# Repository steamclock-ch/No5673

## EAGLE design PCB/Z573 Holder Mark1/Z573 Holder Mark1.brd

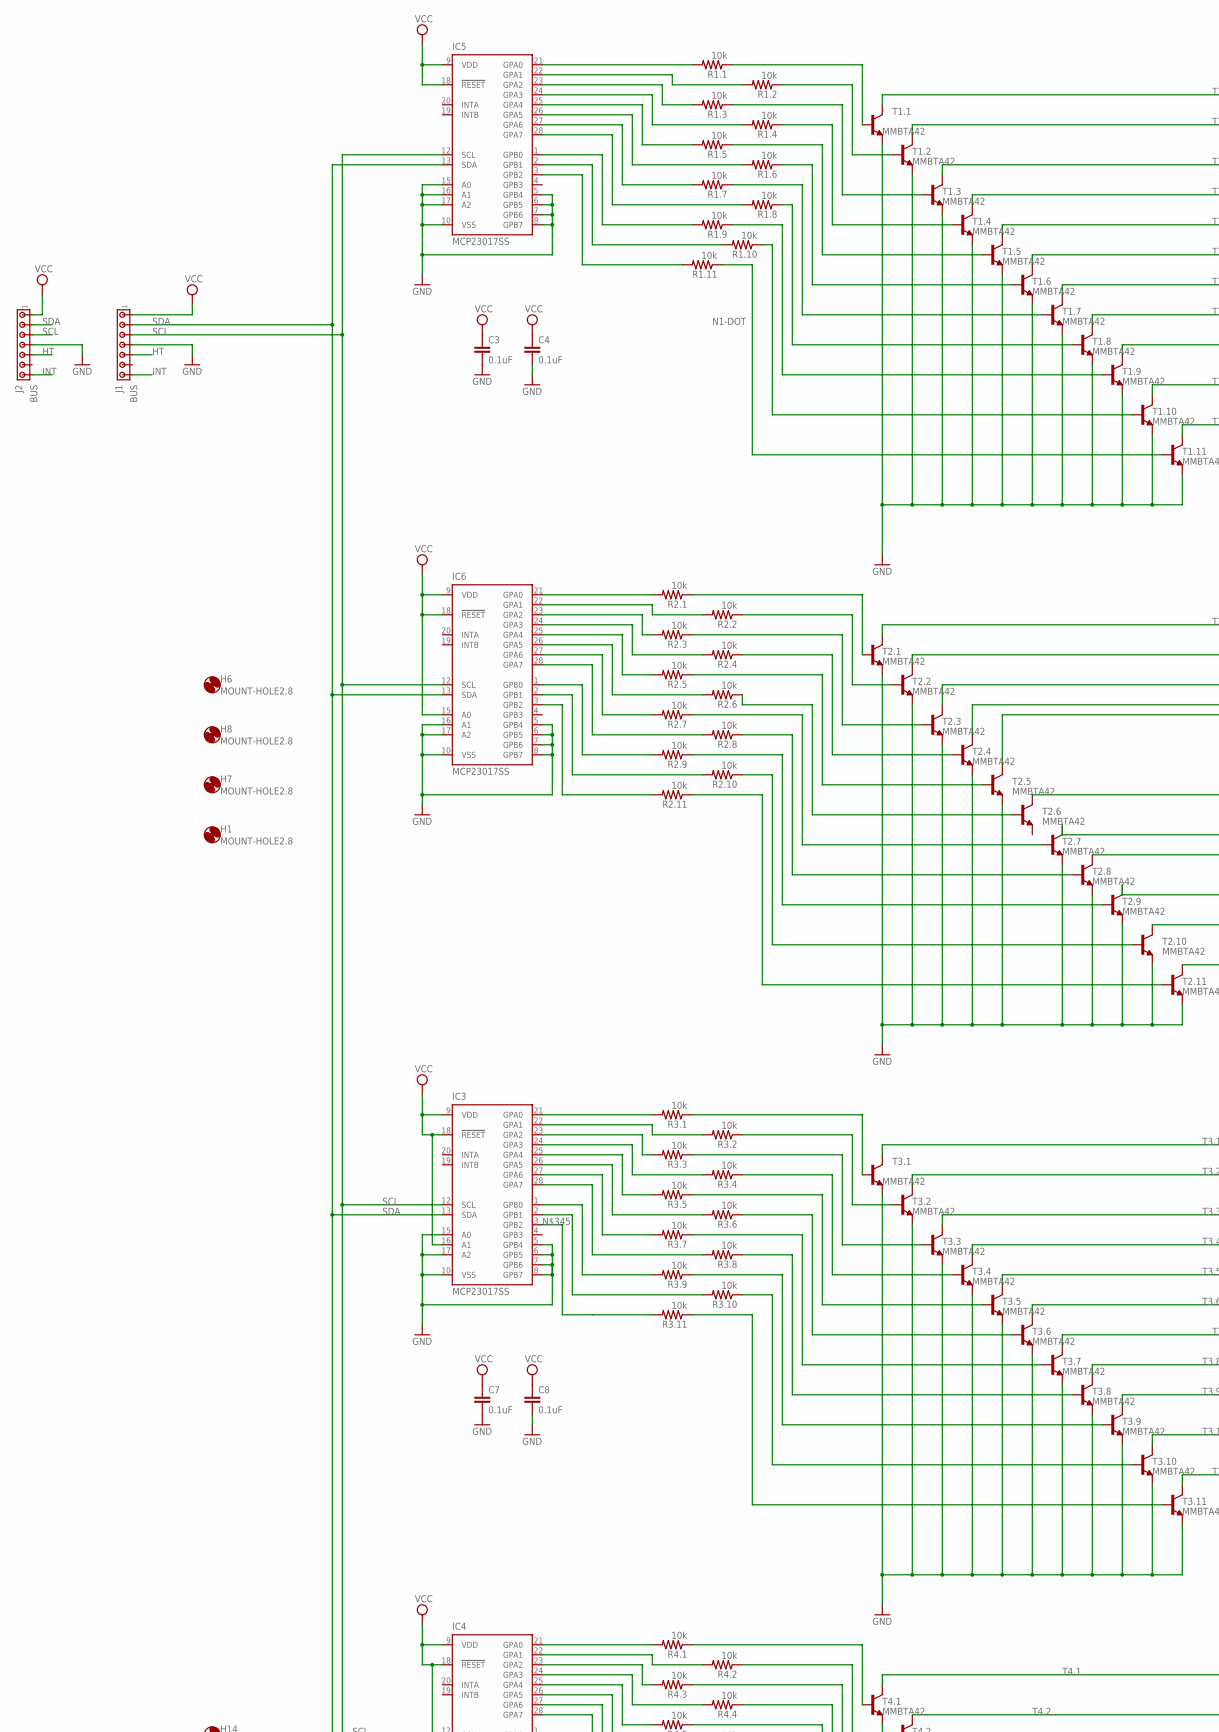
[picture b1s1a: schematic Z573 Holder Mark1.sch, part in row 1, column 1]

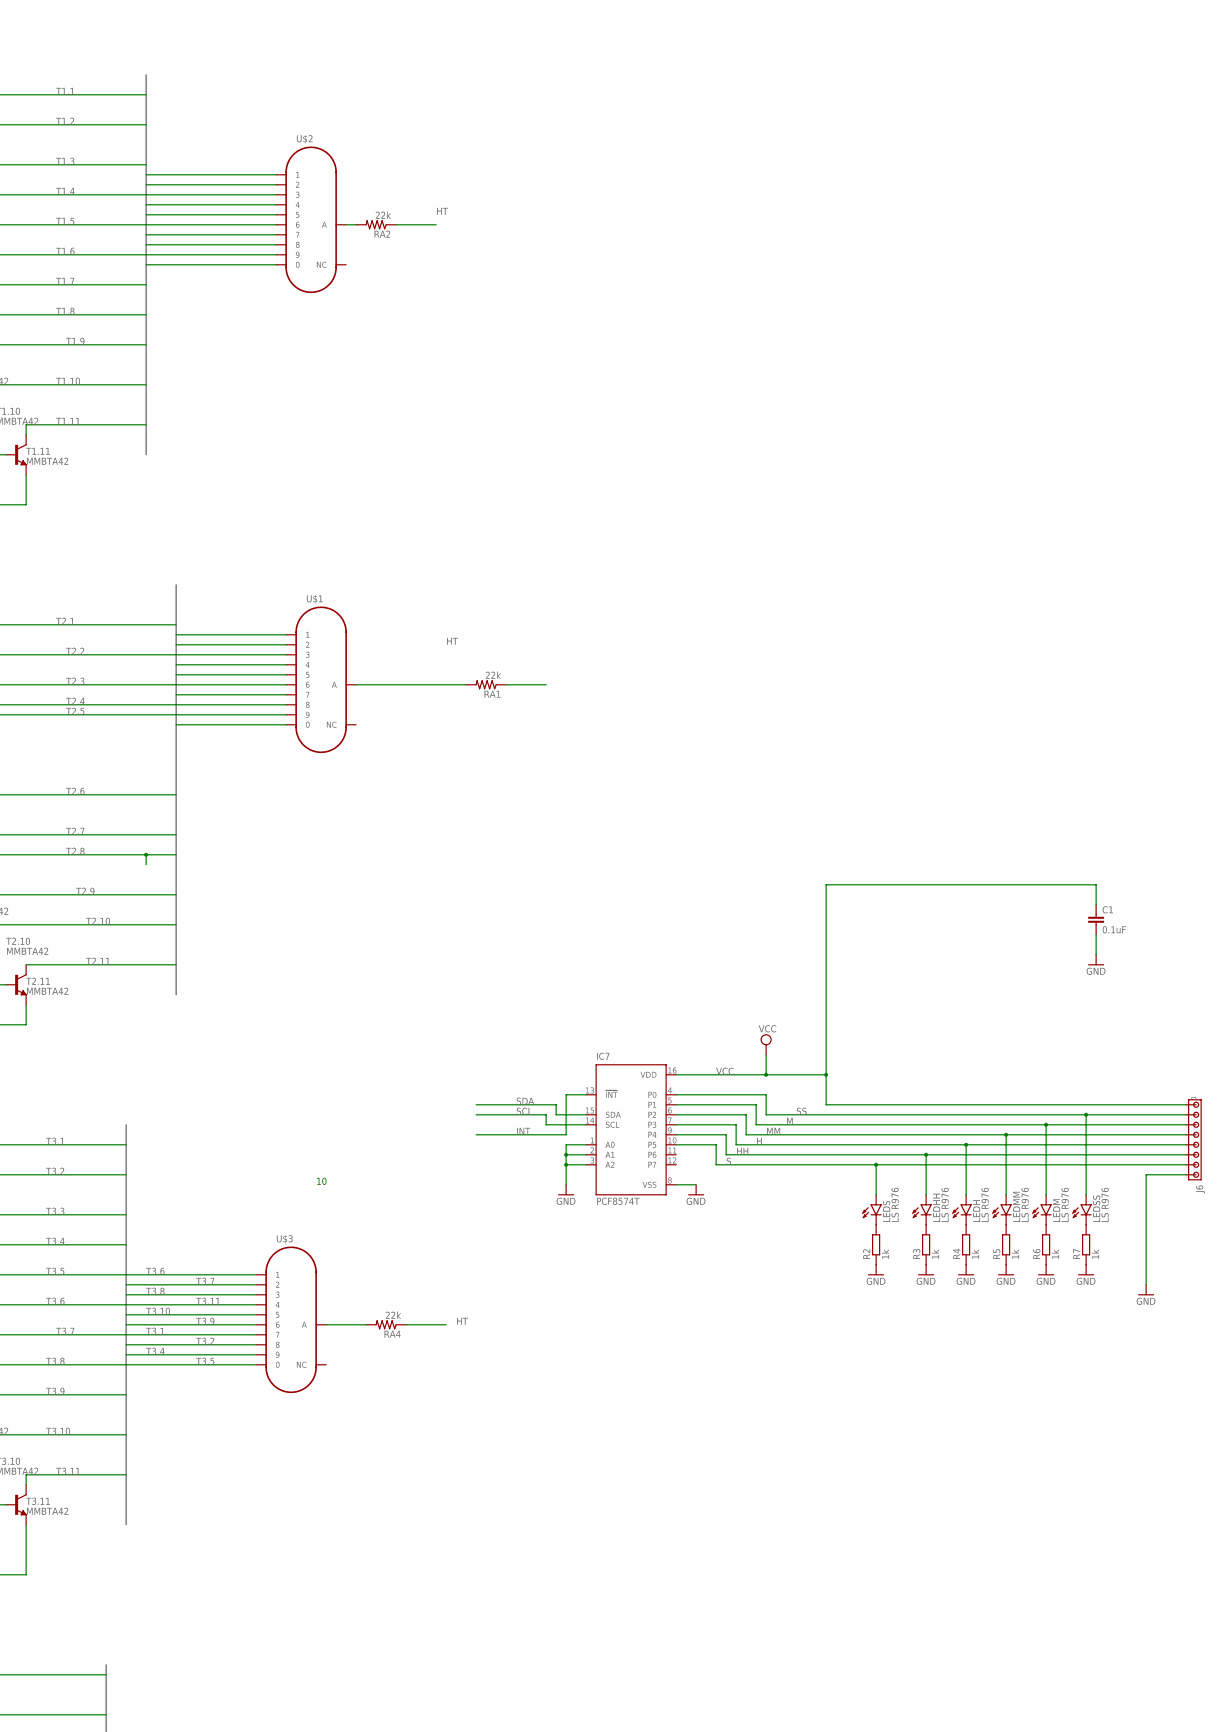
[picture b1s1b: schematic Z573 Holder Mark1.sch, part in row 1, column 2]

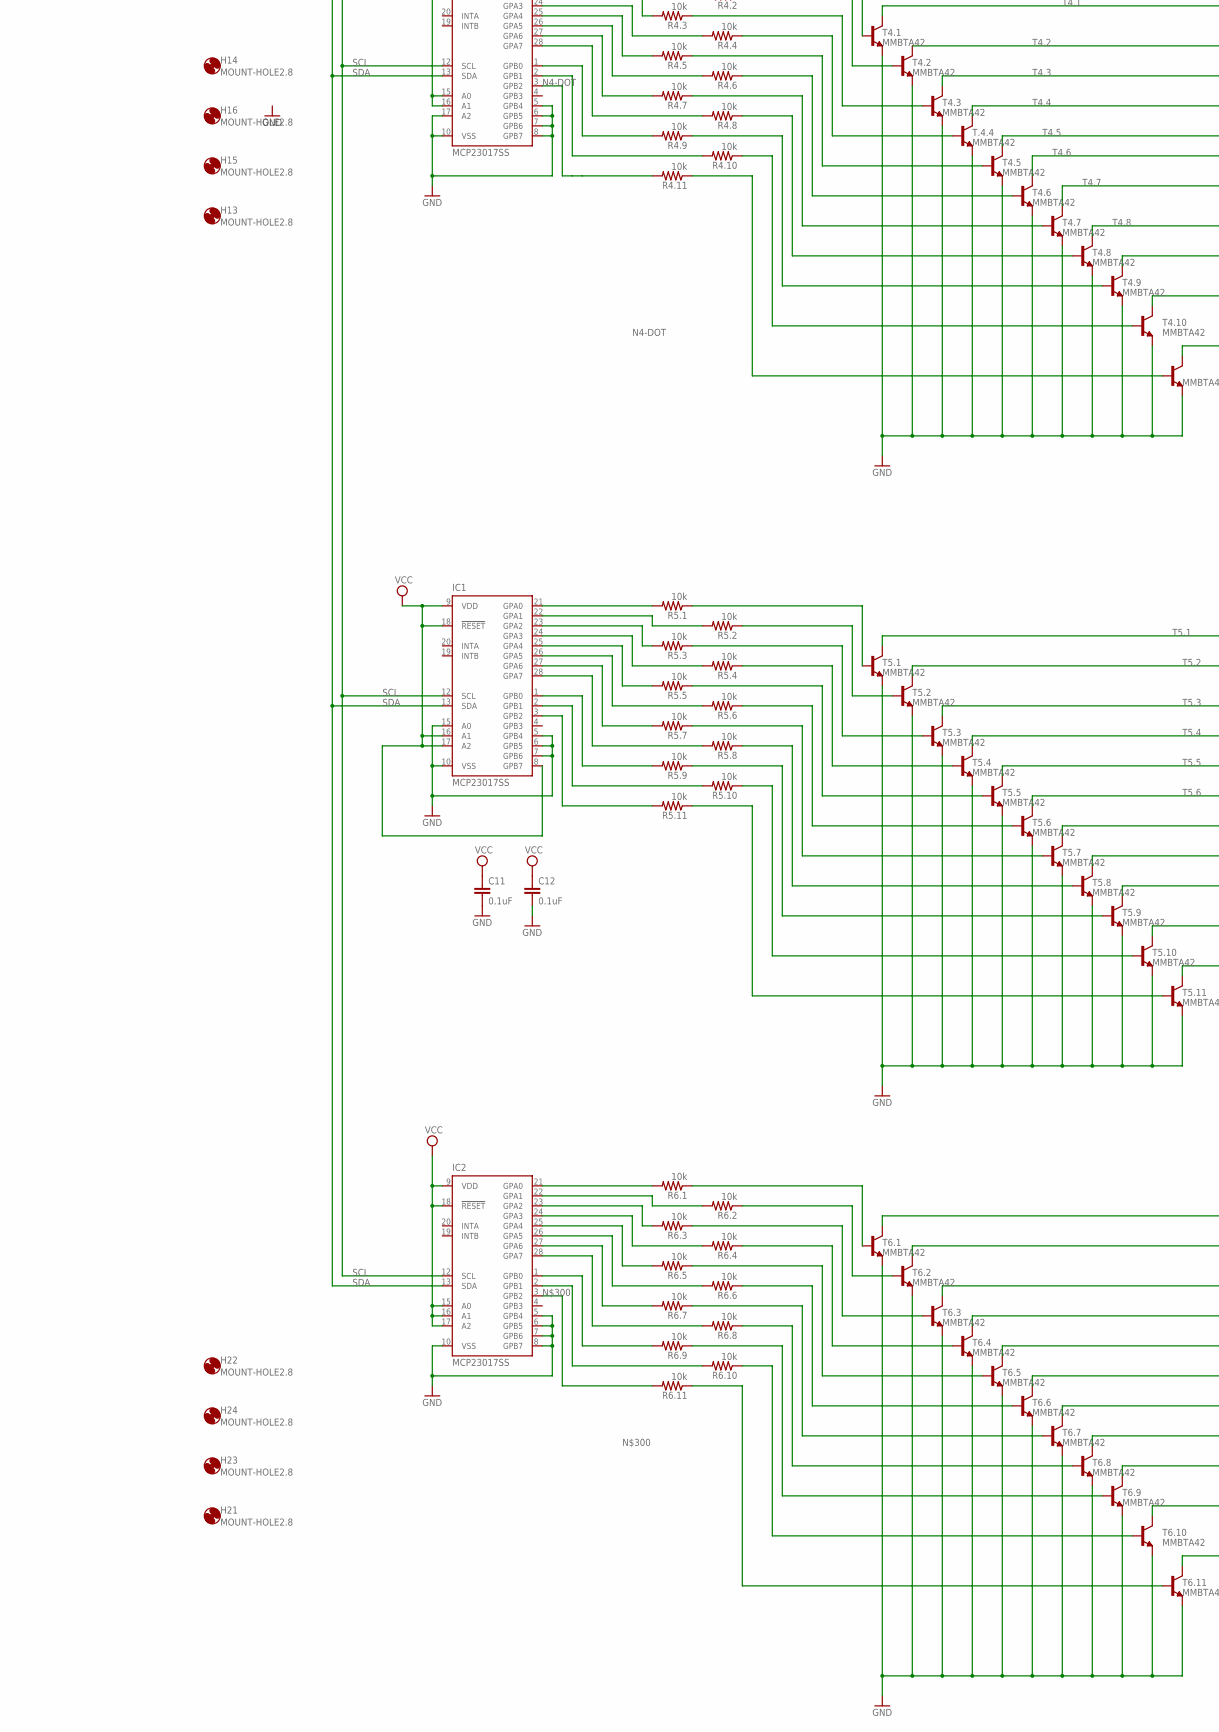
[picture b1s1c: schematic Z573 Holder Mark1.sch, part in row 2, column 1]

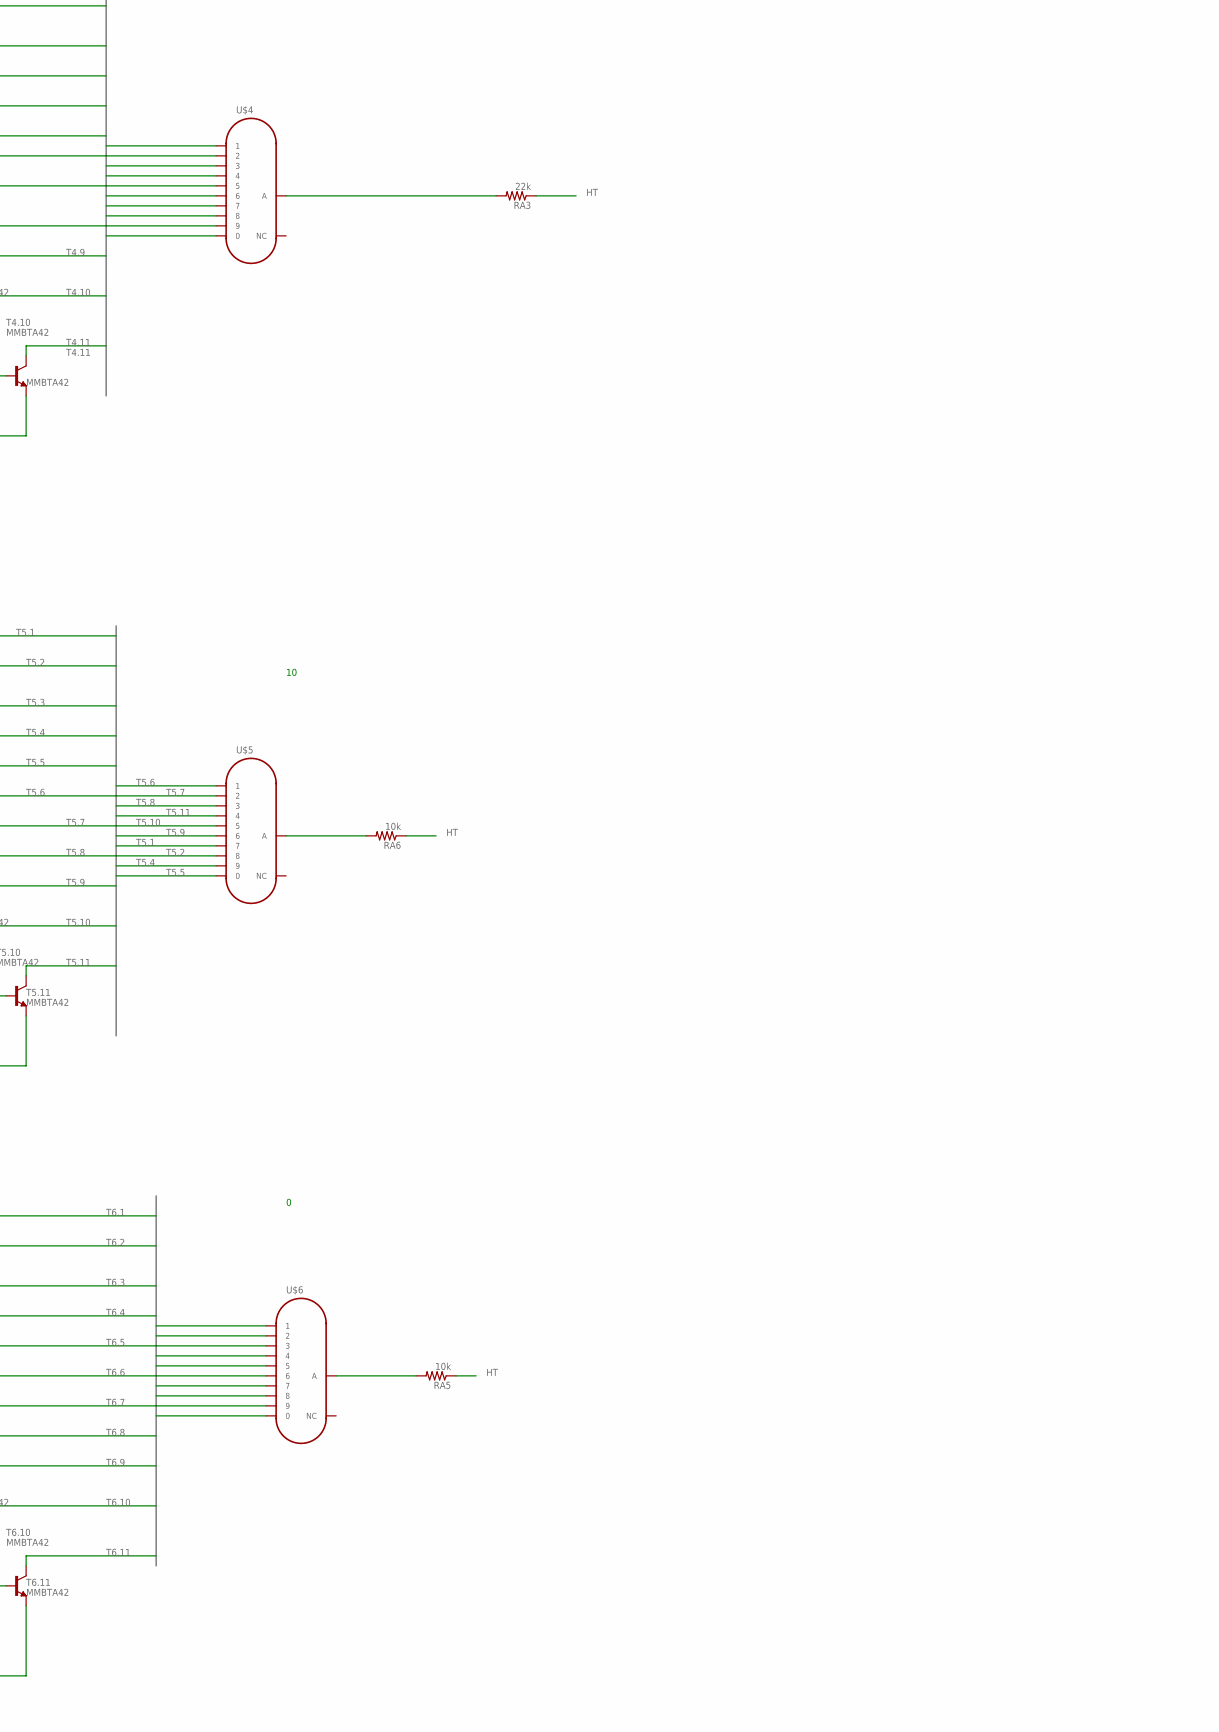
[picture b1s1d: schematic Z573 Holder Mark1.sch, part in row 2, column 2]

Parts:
C1, C3, C4, C7, C8, C11, C12: 0.1uF; C0805
H1, H6, H7, H8, H13, H14, H15, H16, H21, H22, H23, H24: MOUNT-HOLE2.8; 2,8
IC1, IC2, IC3, IC4, IC5, IC6: MCP23017SS; SSOP28
IC7: PCF8574T; SO16W
J1, J2: BUS; 10X07MTA
J6: MTA08-100; 10X08MTA
LEDH: LS R976; SML0805
LEDHH: LS R976; SML0805
LEDM: LS R976; SML0805
LEDMM: LS R976; SML0805
LEDS: LS R976; SML0805
LEDSS: LS R976; SML0805
R1.1, R1.2, R1.3, R1.4, R1.5, R1.6, R1.7, R1.8, R1.9, R1.10, R1.11, R2.1, R2.2, R2.3, R2.4, R2.5, R2.6, R2.7, R2.8, R2.9, R2.10, R2.11, R3.1, R3.2, R3.3, R3.4, R3.5, R3.6, R3.7, R3.8, R3.9, R3.10, R3.11, R4.1, R4.2, R4.3, R4.4, R4.5, R4.6, R4.7, R4.8, R4.9, R4.10, R4.11, R5.1, R5.2, R5.3, R5.4, R5.5, R5.6, R5.7, R5.8, R5.9, R5.10, R5.11, R6.1, R6.2, R6.3, R6.4, R6.5, R6.6, R6.7, R6.8, R6.9, R6.10, R6.11: 10k; R0603
R2, R3, R4, R5, R6, R7: 1k; R0805
RA1, RA2, RA3, RA4: 22k; M0805
RA5, RA6: 10k; M0805
T1.1, T1.2, T1.3, T1.4, T1.5, T1.6, T1.7, T1.8, T1.9, T1.10, T1.11, T2.1, T2.2, T2.3, T2.4, T2.5, T2.6, T2.7, T2.8, T2.9, T2.10, T2.11, T3.1, T3.2, T3.3, T3.4, T3.5, T3.6, T3.7, T3.8, T3.9, T3.10, T3.11, T4.1, T4.2, T4.3, T4.5, T4.6, T4.7, T4.8, T4.9, T4.10, T4.11, T5.1, T5.2, T5.3, T5.4, T5.5, T5.6, T5.7, T5.8, T5.9, T5.10, T5.11, T6.1, T6.2, T6.3, T6.4, T6.5, T6.6, T6.7, T6.8, T6.9, T6.10, T6.11, T.4.4: MMBTA42; SOT23
U$1, U$2, U$3, U$4, U$5, U$6: Z573; Z573M

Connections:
2-E10: R2.2.1, T2.2.1 (B)
2-E11: R2.3.1, T2.3.1 (B)
2-E12: R2.4.1, T2.4.1 (B)
2-E13: R2.5.1, T2.5.1 (B)
2-E15: R2.7.1, T2.7.1 (B)
2-E16: R2.8.1, T2.8.1 (B)
2-E17: R2.9.1, T2.9.1 (B)
2-E18: R2.10.1, T2.10.1 (B)
2-E19: R2.1.1, T2.1.1 (B)
2-E30: R4.2.1, T4.2.1 (B)
2-E31: R4.3.1, T4.3.1 (B)
2-E32: R4.4.1, T.4.4.1 (B)
2-E33: R4.5.1, T4.5.1 (B)
2-E34: R4.6.1, T4.6.1 (B)
2-E35: R4.7.1, T4.7.1 (B)
2-E36: R4.8.1, T4.8.1 (B)
2-E37: R4.9.1, T4.9.1 (B)
2-E38: R4.10.1, T4.10.1 (B)
2-E39: R4.1.1, T4.1.1 (B)
2-E50: R6.2.1, T6.2.1 (B)
2-E51: R6.3.1, T6.3.1 (B)
2-E52: R6.4.1, T6.4.1 (B)
2-E53: R6.5.1, T6.5.1 (B)
2-E54: R6.6.1, T6.6.1 (B)
2-E55: R6.7.1, T6.7.1 (B)
2-E56: R6.8.1, T6.8.1 (B)
2-E57: R6.9.1, T6.9.1 (B)
2-E58: R6.10.1, T6.10.1 (B)
2-E59: R6.1.1, T6.1.1 (B)
2-R12: IC6.23 (GPA2), R2.3.2
2-R16: IC6.27 (GPA6), R2.7.2
2-R17: IC6.28 (GPA7), R2.8.2
2-R18: IC6.1 (GPB0), R2.9.2
2-R19: IC6.2 (GPB1), R2.10.2
2-R30: IC4.21 (GPA0), R4.1.2
2-R31: IC4.22 (GPA1), R4.2.2
2-R32: IC4.23 (GPA2), R4.3.2
2-R33: IC4.24 (GPA3), R4.4.2
2-R34: IC4.25 (GPA4), R4.5.2
2-R35: IC4.26 (GPA5), R4.6.2
2-R36: IC4.27 (GPA6), R4.7.2
2-R37: IC4.28 (GPA7), R4.8.2
2-R38: IC4.1 (GPB0), R4.9.2
2-R39: IC4.2 (GPB1), R4.10.2
2-R50: IC2.21 (GPA0), R6.1.2
2-R51: IC2.22 (GPA1), R6.2.2
2-R52: IC2.23 (GPA2), R6.3.2
2-R53: IC2.24 (GPA3), R6.4.2
2-R54: IC2.25 (GPA4), R6.5.2
2-R55: IC2.26 (GPA5), R6.6.2
2-R56: IC2.27 (GPA6), R6.7.2
2-R57: IC2.28 (GPA7), R6.8.2
2-R58: IC2.1 (GPB0), R6.9.2
2-R59: IC2.2 (GPB1), R6.10.2
GND: C1.2, C3.2, C4.2, C7.2, C8.2, C11.2, C12.2, IC1.5 (GPB4), IC1.6 (GPB5), IC1.7 (GPB6), IC1.10 (VSS), IC1.15 (A0), IC2.5 (GPB4), IC2.6 (GPB5), IC2.7 (GPB6), IC2.8 (GPB7), IC2.10 (VSS), IC3.5 (GPB4), IC3.6 (GPB5), IC3.7 (GPB6), IC3.8 (GPB7), IC3.10 (VSS), IC3.15 (A0), IC3.17 (A2), IC4.5 (GPB4), IC4.6 (GPB5), IC4.7 (GPB6), IC4.8 (GPB7), IC4.10 (VSS), IC4.17 (A2), IC5.5 (GPB4), IC5.6 (GPB5), IC5.7 (GPB6), IC5.8 (GPB7), IC5.10 (VSS), IC5.15 (A0), IC5.16 (A1), IC5.17 (A2), IC6.5 (GPB4), IC6.6 (GPB5), IC6.7 (GPB6), IC6.8 (GPB7), IC6.10 (VSS), IC6.16 (A1), IC6.17 (A2), IC7.1 (A0), IC7.2 (A1), IC7.3 (A2), IC7.8 (VSS), J1.4, J2.4, J6.8, R2.1, R3.1, R4.1, R5.1, R6.1, R7.1, T1.1.2 (E), T1.2.2 (E), T1.3.2 (E), T1.4.2 (E), T1.5.2 (E), T1.6.2 (E), T1.7.2 (E), T1.8.2 (E), T1.9.2 (E), T1.10.2 (E), T1.11.2 (E), T2.1.2 (E), T2.2.2 (E), T2.3.2 (E), T2.4.2 (E), T2.5.2 (E), T2.7.2 (E), T2.8.2 (E), T2.9.2 (E), T2.10.2 (E), T2.11.2 (E), T3.1.2 (E), T3.2.2 (E), T3.3.2 (E), T3.4.2 (E), T3.5.2 (E), T3.6.2 (E), T3.7.2 (E), T3.8.2 (E), T3.9.2 (E), T3.10.2 (E), T3.11.2 (E), T4.1.2 (E), T4.2.2 (E), T4.3.2 (E), T4.5.2 (E), T4.6.2 (E), T4.7.2 (E), T4.8.2 (E), T4.9.2 (E), T4.10.2 (E), T4.11.2 (E), T5.1.2 (E), T5.2.2 (E), T5.3.2 (E), T5.4.2 (E), T5.5.2 (E), T5.6.2 (E), T5.7.2 (E), T5.8.2 (E), T5.9.2 (E), T5.10.2 (E), T5.11.2 (E), T6.1.2 (E), T6.2.2 (E), T6.3.2 (E), T6.4.2 (E), T6.5.2 (E), T6.6.2 (E), T6.7.2 (E), T6.8.2 (E), T6.9.2 (E), T6.10.2 (E), T6.11.2 (E), T.4.4.2 (E)
H: IC7.7 (P3), J6.5, LEDH.A
HH: IC7.9 (P4), J6.6, LEDHH.A
HT: J1.5, J2.5, RA1.1, RA2.1, RA3.1, RA4.1, RA5.1, RA6.1
INT: IC7.13 (!INT), J1.7, J2.7
M: IC7.5 (P1), J6.3, LEDM.A
MM: IC7.6 (P2), J6.4, LEDMM.A
N1-DOT: IC5.3 (GPB2), R1.11.2
N4-DOT: IC4.3 (GPB2), R4.11.2
unnamed: IC6.24 (GPA3), R2.4.2
unnamed: IC6.21 (GPA0), R2.1.2
unnamed: IC5.24 (GPA3), R1.4.2
unnamed: IC6.22 (GPA1), R2.2.2
unnamed: IC5.26 (GPA5), R1.6.2
unnamed: IC5.27 (GPA6), R1.7.2
unnamed: IC5.28 (GPA7), R1.8.2
unnamed: IC5.1 (GPB0), R1.9.2
unnamed: IC5.2 (GPB1), R1.10.2
unnamed: IC6.3 (GPB2), R2.11.2
unnamed: R2.11.1, T2.11.1 (B)
unnamed: RA2.2, U$2.P$13 (A)
unnamed: IC5.21 (GPA0), R1.1.2
unnamed: IC6.25 (GPA4), R2.5.2
unnamed: RA4.2, U$3.P$13 (A)
unnamed: IC6.26 (GPA5), R2.6.2
unnamed: R2.6.1, T2.6.1 (B)
unnamed: R1.2.1, T1.2.1 (B)
unnamed: LEDS.C, R2.2
unnamed: LEDHH.C, R3.2
unnamed: LEDH.C, R4.2
unnamed: LEDMM.C, R5.2
unnamed: LEDM.C, R6.2
unnamed: LEDSS.C, R7.2
unnamed: R1.3.1, T1.3.1 (B)
unnamed: R1.4.1, T1.4.1 (B)
unnamed: R1.5.1, T1.5.1 (B)
unnamed: R1.6.1, T1.6.1 (B)
unnamed: R1.7.1, T1.7.1 (B)
unnamed: R1.8.1, T1.8.1 (B)
unnamed: R1.9.1, T1.9.1 (B)
unnamed: R1.10.1, T1.10.1 (B)
unnamed: R1.1.1, T1.1.1 (B)
unnamed: IC5.22 (GPA1), R1.2.2
unnamed: IC5.23 (GPA2), R1.3.2
unnamed: IC5.25 (GPA4), R1.5.2
unnamed: RA1.2, U$1.P$13 (A)
unnamed: R1.11.1, T1.11.1 (B)
unnamed: R3.2.1, T3.2.1 (B)
unnamed: R3.3.1, T3.3.1 (B)
unnamed: R3.4.1, T3.4.1 (B)
unnamed: R3.5.1, T3.5.1 (B)
unnamed: R3.6.1, T3.6.1 (B)
unnamed: R3.7.1, T3.7.1 (B)
unnamed: R3.8.1, T3.8.1 (B)
unnamed: R3.9.1, T3.9.1 (B)
unnamed: R3.10.1, T3.10.1 (B)
unnamed: R3.1.1, T3.1.1 (B)
unnamed: IC3.21 (GPA0), R3.1.2
unnamed: IC3.22 (GPA1), R3.2.2
unnamed: IC3.23 (GPA2), R3.3.2
unnamed: IC3.24 (GPA3), R3.4.2
unnamed: IC3.25 (GPA4), R3.5.2
unnamed: IC3.26 (GPA5), R3.6.2
unnamed: IC3.27 (GPA6), R3.7.2
unnamed: IC3.28 (GPA7), R3.8.2
unnamed: IC3.1 (GPB0), R3.9.2
unnamed: IC3.2 (GPB1), R3.10.2
unnamed: RA3.2, U$4.P$13 (A)
unnamed: R3.11.1, T3.11.1 (B)
unnamed: R4.11.1, T4.11.1 (B)
unnamed: R5.2.1, T5.2.1 (B)
unnamed: R5.3.1, T5.3.1 (B)
unnamed: R5.4.1, T5.4.1 (B)
unnamed: R5.5.1, T5.5.1 (B)
unnamed: R5.6.1, T5.6.1 (B)
unnamed: R5.7.1, T5.7.1 (B)
unnamed: R5.8.1, T5.8.1 (B)
unnamed: R5.9.1, T5.9.1 (B)
unnamed: R5.10.1, T5.10.1 (B)
unnamed: R5.1.1, T5.1.1 (B)
unnamed: IC1.21 (GPA0), R5.1.2
unnamed: IC1.22 (GPA1), R5.2.2
unnamed: IC1.23 (GPA2), R5.3.2
unnamed: IC1.24 (GPA3), R5.4.2
unnamed: IC1.25 (GPA4), R5.5.2
unnamed: IC1.26 (GPA5), R5.6.2
unnamed: IC1.27 (GPA6), R5.7.2
unnamed: IC1.28 (GPA7), R5.8.2
unnamed: IC1.1 (GPB0), R5.9.2
unnamed: IC1.2 (GPB1), R5.10.2
unnamed: RA5.2, U$6.P$13 (A)
unnamed: R5.11.1, T5.11.1 (B)
unnamed: R6.11.1, T6.11.1 (B)
unnamed: RA6.2, U$5.P$13 (A)
unnamed: IC1.3 (GPB2), R5.11.2
unnamed: IC2.3 (GPB2), R6.11.2
unnamed: IC3.3 (GPB2), R3.11.2
S: IC7.10 (P5), J6.7, LEDS.A
SCL: IC1.12 (SCL), IC2.12 (SCL), IC3.12 (SCL), IC4.12 (SCL), IC5.12 (SCL), IC6.12 (SCL), IC7.14 (SCL), J1.3, J2.3
SDA: IC1.13 (SDA), IC2.13 (SDA), IC3.13 (SDA), IC4.13 (SDA), IC5.13 (SDA), IC6.13 (SDA), IC7.15 (SDA), J1.2, J2.2
SS: IC7.4 (P0), J6.2, LEDSS.A
T1.1: T1.1.3 (C), U$2.P$8 (7)
T1.2: T1.2.3 (C), U$2.P$9 (8)
T1.3: T1.3.3 (C)
T1.4: T1.4.3 (C), U$2.P$11 (9)
T1.5: T1.5.3 (C), U$2.P$12 (0)
T1.6: T1.6.3 (C), U$2.P$1 (1)
T1.7: T1.7.3 (C), U$2.P$2 (2)
T1.8: T1.8.3 (C), U$2.P$3 (3)
T1.9: T1.9.3 (C), U$2.P$7 (6)
T1.10: T1.10.3 (C), U$2.P$6 (5)
T1.11: T1.11.3 (C), U$2.P$5 (4)
T2.1: T2.1.3 (C), U$1.P$7 (6)
T2.2: T2.2.3 (C), U$1.P$6 (5)
T2.3: T2.3.3 (C), U$1.P$5 (4)
T2.4: T2.4.3 (C), U$1.P$3 (3)
T2.5: T2.5.3 (C), U$1.P$2 (2)
T2.6: T2.6.3 (C), U$1.P$1 (1)
T2.7: T2.7.3 (C), U$1.P$12 (0)
T2.8: T2.8.3 (C), U$1.P$11 (9)
T2.9: T2.9.3 (C), U$1.P$8 (7)
T2.10: T2.10.3 (C), U$1.P$9 (8)
T2.11: T2.11.3 (C)
T3.1: T3.1.3 (C), U$3.P$8 (7)
T3.2: T3.2.3 (C), U$3.P$9 (8)
T3.3: T3.3.3 (C)
T3.4: T3.4.3 (C), U$3.P$11 (9)
T3.5: T3.5.3 (C), U$3.P$12 (0)
T3.6: T3.6.3 (C), U$3.P$1 (1)
T3.7: T3.7.3 (C), U$3.P$2 (2)
T3.8: T3.8.3 (C), U$3.P$3 (3)
T3.9: T3.9.3 (C), U$3.P$7 (6)
T3.10: T3.10.3 (C), U$3.P$6 (5)
T3.11: T3.11.3 (C), U$3.P$5 (4)
T4.1: T4.1.3 (C), U$4.P$7 (6)
T4.2: T4.2.3 (C), U$4.P$6 (5)
T4.3: T4.3.3 (C), U$4.P$5 (4)
T4.4: T.4.4.3 (C), U$4.P$3 (3)
T4.5: T4.5.3 (C), U$4.P$2 (2)
T4.6: T4.6.3 (C), U$4.P$1 (1)
T4.7: T4.7.3 (C), U$4.P$12 (0)
T4.8: T4.8.3 (C), U$4.P$11 (9)
T4.9: T4.9.3 (C), U$4.P$8 (7)
T4.10: T4.10.3 (C), U$4.P$9 (8)
T4.11: T4.11.3 (C)
T5.1: T5.1.3 (C), U$5.P$8 (7)
T5.2: T5.2.3 (C), U$5.P$9 (8)
T5.3: T5.3.3 (C)
T5.4: T5.4.3 (C), U$5.P$11 (9)
T5.5: T5.5.3 (C), U$5.P$12 (0)
T5.6: T5.6.3 (C), U$5.P$1 (1)
T5.7: T5.7.3 (C), U$5.P$2 (2)
T5.8: T5.8.3 (C), U$5.P$3 (3)
T5.9: T5.9.3 (C), U$5.P$7 (6)
T5.10: T5.10.3 (C), U$5.P$6 (5)
T5.11: T5.11.3 (C), U$5.P$5 (4)
T6.1: T6.1.3 (C), U$6.P$7 (6)
T6.2: T6.2.3 (C), U$6.P$6 (5)
T6.3: T6.3.3 (C), U$6.P$5 (4)
T6.4: T6.4.3 (C), U$6.P$3 (3)
T6.5: T6.5.3 (C), U$6.P$2 (2)
T6.6: T6.6.3 (C), U$6.P$1 (1)
T6.7: T6.7.3 (C), U$6.P$12 (0)
T6.8: T6.8.3 (C), U$6.P$11 (9)
T6.9: T6.9.3 (C), U$6.P$8 (7)
T6.10: T6.10.3 (C), U$6.P$9 (8)
T6.11: T6.11.3 (C)
VCC: C1.1, C3.1, C4.1, C7.1, C8.1, C11.1, C12.1, IC1.8 (GPB7), IC1.9 (VDD), IC1.16 (A1), IC1.17 (A2), IC1.18 (!RESET), IC2.9 (VDD), IC2.15 (A0), IC2.16 (A1), IC2.17 (A2), IC2.18 (!RESET), IC3.9 (VDD), IC3.16 (A1), IC3.18 (!RESET), IC4.9 (VDD), IC4.15 (A0), IC4.16 (A1), IC4.18 (!RESET), IC5.9 (VDD), IC5.18 (!RESET), IC6.9 (VDD), IC6.15 (A0), IC6.18 (!RESET), IC7.16 (VDD), J1.1, J2.1, J6.1

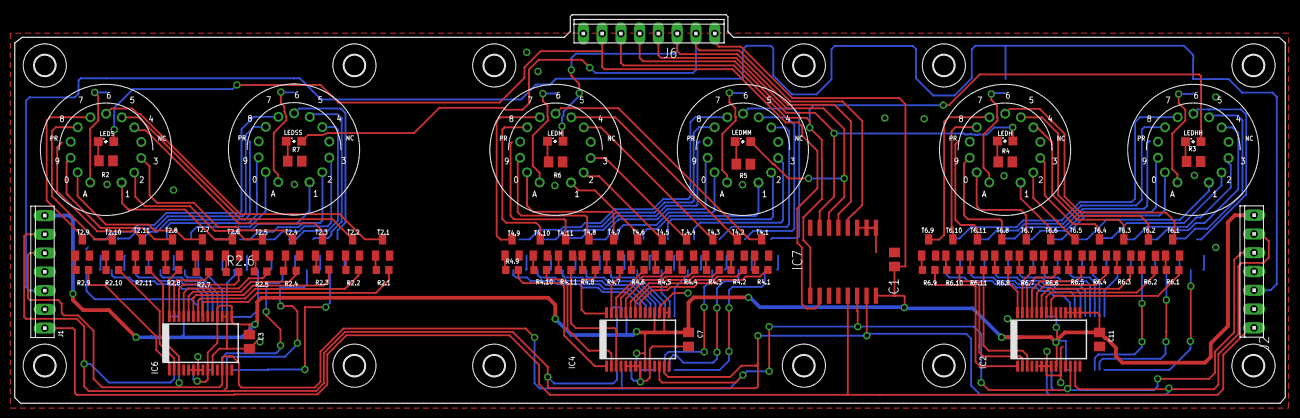
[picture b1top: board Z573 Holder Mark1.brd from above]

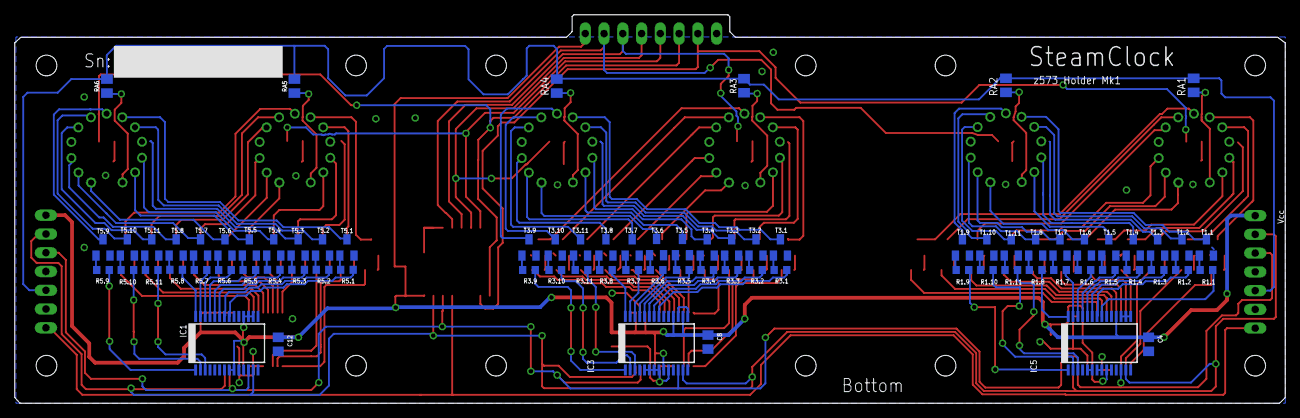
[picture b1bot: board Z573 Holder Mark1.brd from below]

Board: 2 copper layers, 172.0 x 52.6 mm, 185 parts (78 on the bottom side), 216 nets.

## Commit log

2022-07-02 init
